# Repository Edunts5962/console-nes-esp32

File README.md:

# Console NES ESP32

Une console NES portable construite autour d'un **ESP32-S3** à écran tactile : émulation des jeux NES avec le son, menus modernes, jeux sur carte microSD ou en mémoire interne, sauvegardes, manette NES filaire **ou téléphone Android comme manette Bluetooth**, **sortie télévision** en vidéo composite grâce à un second ESP32, et portail web pour envoyer les jeux et mettre le logiciel à jour par Wi-Fi.

> Projet amateur, en version bêta. Dérivé du dépôt [Esp32-S3-nes-emulator-by-DSN](https://github.com/derdacavga/Esp32-S3-nes-emulator-by-DSN) (derdacavga), lui-même basé sur le cœur d'émulation **nofrendo**. Aucun jeu n'est fourni.

## Sommaire

- [Fonctionnalités](#fonctionnalités)
- [Matériel](#matériel)
- [Contenu du dépôt](#contenu-du-dépôt)
- [Installation](#installation)
- [Premiers pas](#premiers-pas)
- [Manette sur le téléphone](#manette-sur-le-téléphone)
- [Options de compilation](#options-de-compilation)
- [Limites connues](#limites-connues)
- [Crédits et licences](#crédits-et-licences)

## Fonctionnalités

**Jeux**
- Émulation NES (cœur nofrendo) avec le son ; 49 mappers : 0 à 5, 7 à 11, 15, 16, 18, 19, 21 à 25, 32 à 34, 40 à 42, 46, 50, 64 à 66, 69 à 71, 73, 75, 78, 79, 85, 87, 93, 94, 99, 113, 118, 160, 229, 231, 232. Un jeu non pris en charge est refusé avec un message.
- Jeux sur **carte microSD** et en **mémoire interne** (partition FAT de la flash, ~9,6 Mo) ; jusqu'à **1000 jeux**, affichés par pages de 50.
- **Sauvegardes** : RAM de pile des cartouches (Zelda, Final Fantasy…), sauvegarde instantanée sur 3 emplacements, **reprise automatique** en quittant un jeu.
- **Menu pause** en partie : reprendre, sauvegarder, charger, volume, favoris, jeux récents, changer de jeu sans redémarrer.
- Un jeu qui fait planter la console au lancement est **mis de côté** (dossier `/quarantaine`), récupérable ensuite.

**Interface**
- Menus **LVGL 8** sur l'écran tactile 320 × 240 : liste des jeux avec recherche (clavier à l'écran), favoris, récents, « Reprendre » ; Réglages (luminosité, volume, thèmes de couleurs, Wi-Fi, étalonnage du tactile, aide) ; onglets Vidéo et Portail (QR codes).
- Trois manettes, utilisables ensemble : **zones tactiles** de part et d'autre de l'image, **manette NES filaire** (registre CD4021, prise DB9), **téléphone Android** en Bluetooth LE (page web [`manette8.html`](docs/manette/manette8.html)).
- **Plein écran** automatique quand le téléphone sert de manette.

**Télévision**
- **Sortie vidéo composite couleur** PAL 50 Hz, NTSC ou PAL 60 Hz, image progressive au choix, et son, par un second ESP32 relié en SPI (3 fils).
- Liste des jeux et menu pause affichés sur la télévision.

**Wi-Fi**
- Connexion à la box ou **point d'accès** « NES-WiFi » de la console.
- **Portail web** : envoi de jeux (glisser-déposer), déplacement carte SD ↔ mémoire interne, suppression, recherche de doublons, formatage de la carte SD, jeux écartés, réseau Wi-Fi de la box.
- **Mise à jour du logiciel par Wi-Fi** (fichier `.bin` envoyé au portail) : jeux, sauvegardes et réglages sont conservés.

| Page du téléphone | Portail web |
|---|---|
|  |  |

## Matériel

### Carte principale — LCDWIKI ES3C28P

| | |
|---|---|
| Processeur | **ESP32-S3R8** : 2 cœurs Xtensa LX7 à 240 MHz, 512 Ko de SRAM, **8 Mo de PSRAM** octale (OPI) |
| Flash | **16 Mo** |
| Écran | **ILI9341 2,8"**, 320 × 240, SPI |
| Tactile | **FT6336**, capacitif (I2C) |
| Son | codec **ES8311** (I2C + I2S) et amplificateur, haut-parleur |
| Stockage | lecteur **microSD** (SD_MMC) |
| Radio | Wi-Fi 2,4 GHz, Bluetooth LE |

### Carte vidéo — ESP32 « classique » (facultative)

| | |
|---|---|
| Carte | **Freenove ESP32-WROOM** (module ESP32-WROOM-32E) ou ESP32-DevKitC V4 |
| Processeur | ESP32-D0WD-V3 : 2 cœurs Xtensa LX6 à 240 MHz, 520 Ko de SRAM, 4 Mo de flash |
| Vidéo | composite couleur sur **GPIO25** (DAC intégré), vers l'entrée AV d'un téléviseur ou un convertisseur AV → HDMI |
| Son | **GPIO26** en PWM + filtre RC |

Seul l'ESP32 d'origine a le DAC nécessaire à la vidéo : un ESP32-S2, S3 ou C3 ne convient pas pour cette carte.

### Câblage minimal

| ESP32-S3 (ES3C28P) | | Carte vidéo ESP32 |
|---|---|---|
| GPIO2 (connecteur « Expanded IO ») | SCLK, 330 Ω | IO14 |
| GPIO3 (connecteur « Expanded IO ») | CS, 330 Ω | IO15 |
| GPIO43 / TX0 (connecteur « UART ») | MOSI, 330 Ω | IO13 |
| GND | masse | GND |

Manette NES filaire (3,3 V) : LATCH → GPIO21, CLOCK → GPIO14, DATA → GPIO44 (RX0).

Le document [docs/MATERIEL.md](docs/MATERIEL.md) détaille tout : brochage complet, sortie vidéo (pourquoi GPIO25 va directement à la prise RCA), manette, **carte porteuse KiCad** qui réunit les deux cartes (alimentation 9–12 V, prises RCA, DB9), listes d'achat, mise en service et dépannage.

## Contenu du dépôt

```
console-nes-esp32/
├── firmware/
│   ├── nes_emulator/         croquis de la console (ESP32-S3)
│   └── video_coprocessor/    croquis de la carte vidéo TV (ESP32)
├── prototypes/
│   └── autonome_prototype_v0.4/   essai d'émulateur minimaliste sur un seul ESP32
├── config/
│   ├── lv_conf.h             configuration LVGL 8.3 utilisée
│   └── User_Setup.h          configuration TFT_eSPI de l'écran ES3C28P
├── hardware/kicad/           carte porteuse et manette (KiCad, PDF, nomenclatures, import EasyEDA)
├── docs/
│   ├── MATERIEL.md           matériel, câblage, sortie vidéo, carte porteuse
│   ├── protocole_bluetooth.md  manette du téléphone : utilisation et protocole
│   ├── aide_memoire.html     aide-mémoire des commandes (à imprimer)
│   ├── manette/              page web de la manette du téléphone
│   └── images/
├── CHANGELOG.md
└── LICENSE
```

## Installation

### 1. Outils

- **IDE Arduino 2.x** et le paquet de cartes **esp32 d'Espressif Systems, version 3.x** (compilé avec la 3.3.11).
- Bibliothèques (Gestionnaire de bibliothèques ou copie manuelle dans `Arduino/libraries/`) :

| Bibliothèque | Version | Pour | Configuration |
|---|---|---|---|
| **lvgl** | **8.3.11** (pas la 9.x) | console | copier [`config/lv_conf.h`](config/lv_conf.h) dans `Arduino/libraries/`, à côté du dossier `lvgl` |
| **TFT_eSPI** | 2.5.43 | console | remplacer `Arduino/libraries/TFT_eSPI/User_Setup.h` par [`config/User_Setup.h`](config/User_Setup.h) |
| **LovyanGFX** | 1.2.x | carte vidéo | aucune |

Wi-Fi, Bluetooth, serveur web, mise à jour OTA, NVS, SD_MMC et FFat sont fournis par le paquet esp32.

### 2. Identifiants Wi-Fi

Dans `firmware/nes_emulator/`, copier `wifi_config.example.h` en **`wifi_config.h`** et y mettre le nom et le mot de passe de la box ; changer aussi le mot de passe du point d'accès `NES-WiFi` (8 caractères au moins). `wifi_config.h` est ignoré par git : il ne part pas sur le dépôt. Sans lui, le croquis compile avec le modèle (le point d'accès reste utilisable, et le réseau de la box peut être saisi plus tard dans le portail).

### 3. Console (ESP32-S3)

Ouvrir `firmware/nes_emulator/nes_emulator.ino`, puis dans le menu **Outils** :

| Réglage | Valeur |
|---|---|
| Carte | **ESP32S3 Dev Module** |
| USB CDC On Boot | **Enabled** (le port série passe par l'USB ; GPIO43/44 restent libres pour la liaison vidéo et la manette) |
| Flash Size | **16MB (128Mb)** |
| Partition Scheme | **16M Flash (3MB APP/9.9MB FATFS)** |
| PSRAM | **OPI PSRAM** |

Téléverser. Si le téléversement échoue : maintenir BOOT, appuyer sur RESET, relâcher BOOT.

Avec arduino-cli :

```sh
arduino-cli compile -b "esp32:esp32:esp32s3:PSRAM=opi,FlashSize=16M,CDCOnBoot=cdc,PartitionScheme=app3M_fat9M_16MB" firmware/nes_emulator
```

**Sans carte vidéo**, mettre `ENABLE_VIDEO_LINK` à 0 dans `video_link.h`.

### 4. Carte vidéo (ESP32)

Ouvrir `firmware/video_coprocessor/video_coprocessor.ino`, carte **ESP32 Dev Module**, bibliothèque LovyanGFX, téléverser. Sans console branchée, la télévision affiche « En attente de la console » avec une mire de couleurs ; un appui long sur BOOT change la norme (PAL 50 → NTSC → PAL 60).

```sh
arduino-cli compile -b esp32:esp32:esp32 firmware/video_coprocessor
```

## Premiers pas

1. **Jeux** : copier des fichiers `.nes` à la **racine** d'une carte microSD formatée en **FAT32**, ou les envoyer plus tard par le portail (carte SD ou mémoire interne).
2. **Premier démarrage** : l'écran demande d'étalonner le tactile (toucher 3 croix, puis une croix de vérification).
3. **Jouer** : toucher un jeu. Un appui long ouvre sa fiche (favori, reprendre, supprimer).

| Commande | Pendant le jeu |
|---|---|
| SELECT + START tenus 1 s | menu pause (écran ou télévision) |
| doigt posé 1 s sur l'image | menu pause (écran tactile) |
| SELECT + haut / bas | volume ±5 % |
| SELECT tenu 3 s | retour au menu de la console (la partie est gardée) |

Toutes les commandes sont dans Réglages (aide « Commandes ») et dans l'[aide-mémoire](docs/aide_memoire.html) à imprimer.

### Portail web

1. Réglages > Wi-Fi : allumer le Wi-Fi (mode Auto : la box, puis le point d'accès si elle ne répond pas).
2. L'onglet **Portail** affiche l'adresse et un QR code. En point d'accès : rejoindre le réseau **`NES-WiFi`** (mot de passe défini dans `wifi_config.h`), puis ouvrir **http://192.168.4.1/**.

Le Wi-Fi est coupé au lancement d'un jeu, et il ne fonctionne pas en même temps que la manette Bluetooth (mémoire de l'ESP32-S3 insuffisante pour les deux).

### Mise à jour du logiciel par Wi-Fi

Dans l'IDE Arduino : **Croquis > Exporter les binaires compilés**, puis envoyer le fichier `nes_emulator.ino.bin` dans la section « Mettre à jour le logiciel » du portail. La console redémarre sur la nouvelle version ; jeux, sauvegardes et réglages sont conservés.

> Les fichiers `.bin` compilés contiennent les identifiants Wi-Fi de `wifi_config.h` : ne pas les publier (ils sont ignorés par git).

## Manette sur le téléphone

La page [`docs/manette/manette8.html`](docs/manette/manette8.html) utilise **Web Bluetooth**, qui exige **Chrome sur Android** et une page servie en **HTTPS**. GitHub Pages s'en charge :

1. Sur GitHub, dépôt > **Settings > Pages** ; *Source* : **Deploy from a branch**, branche **main**, dossier **/docs**, *Save*.
2. Quelques minutes plus tard, la page est disponible à l'adresse
   `https://<pseudo>.github.io/console-nes-esp32/manette/manette8.html`.
3. L'ouvrir dans Chrome sur le téléphone (Bluetooth et localisation activés), **CONNECTER**, choisir **`NES-ESP32S3`**. Chrome > ⋮ > « Ajouter à l'écran d'accueil » l'installe comme une application.

Utilisation et protocole : [docs/protocole_bluetooth.md](docs/protocole_bluetooth.md).

## Options de compilation

| Fichier | Option | Défaut | Rôle |
|---|---|---|---|
| `hw_config.h` | `HAS_PHYSICAL_CONTROLLER` | 0 | 1 = manette filaire branchée |
| `hw_config.h` | `PAD_PROTOCOL` | `PAD_PROTOCOL_NES` | manette NES (CD4021) ou montage 74HC165 |
| `hw_config.h` | `USE_TOUCH_CONTROLS` | 1 | zones tactiles pendant le jeu |
| `hw_config.h` | `ENABLE_BLE_GAMEPAD` | 1 | manette du téléphone (0 : pile Bluetooth non compilée, ~230 Ko de moins) |
| `hw_config.h` | `LCD_FULLSCREEN_MODE` | 1 | plein écran : 0 jamais, 1 avec le téléphone, 2 toujours |
| `hw_config.h` | `LCD_FULLSCREEN_CROP_LINES` | 8 | lignes retirées en haut et en bas en plein écran |
| `hw_config.h` | `LCD_GAME_COLOR_FIX` | 1 | ordre des octets des couleurs du jeu sur l'écran |
| `hw_config.h` | `USE_LVGL_UI` | 1 | 0 = ancienne interface dessinée à la main |
| `video_link.h` | `ENABLE_VIDEO_LINK` | 1 | liaison vers la carte vidéo (0 sans carte vidéo) |
| `wifi_boot.h` | `ENABLE_WIFI_PORTAL` | 1 | Wi-Fi et portail web |
| `wifi_boot.h` | `WIFI_START_AT_BOOT` | 0 | 1 = connexion Wi-Fi pendant le logo |
| `video_coprocessor.ino` | `VIDEO_OUTPUT_LEVEL` | 128 | amplitude vidéo : 160–200 si l'image est sombre, 100–110 si elle est trop claire |

## Limites connues

- Logiciel en **version bêta**. Selon les jeux, l'émulateur saute des images pour garder la vitesse du jeu.
- Wi-Fi et Bluetooth ne fonctionnent pas en même temps (le Bluetooth est arrêté tant que le Wi-Fi est allumé).
- Web Bluetooth : Chrome sur Android uniquement (Safari sur iPhone ne le propose pas).
- La **carte porteuse KiCad** est placée mais **pas routée**, et n'a pas été fabriquée.
- Le prototype « autonome » (un seul ESP32) valide le matériel mais n'exécute pas encore de jeu.

## Crédits et licences

- Ce projet est distribué sous licence **GNU GPL v3** ([LICENSE](LICENSE)), comme le dépôt d'origine [derdacavga/Esp32-S3-nes-emulator-by-DSN](https://github.com/derdacavga/Esp32-S3-nes-emulator-by-DSN).
- Cœur d'émulation **nofrendo** © 1998-2000 Matthew Conte, repris via [esp32-nesemu](https://github.com/espressif/esp32-nesemu) d'Espressif : licence GNU LGPL v2 ([LICENSES/LGPL-2.0.txt](LICENSES/LGPL-2.0.txt)), mention de licence d'origine au début de chaque fichier repris.
- Pilote du codec **ES8311** : Espressif Systems, licence Apache-2.0 (en-têtes SPDX conservés, [LICENSES/Apache-2.0.txt](LICENSES/Apache-2.0.txt)).
- Générateur de **QR code** : Project Nayuki, licence MIT (texte dans `nes_qrcodegen.c/.h`).
- Sortie vidéo composite : adaptation de `Panel_CVBS` de [LovyanGFX](https://github.com/lovyan03/LovyanGFX) (lovyan03 et contributeurs), licence FreeBSD (`firmware/video_coprocessor/LICENCE_LovyanGFX.txt`) ; inspirée de [ESP_8_BIT_composite](https://github.com/Roger-random/ESP_8_BIT_composite) (Roger Cheng) et [esp_8_bit](https://github.com/rossumur/esp_8_bit) (rossum).
- Polices de l'interface : **Montserrat** (SIL Open Font License 1.1) et symboles **Font Awesome Free** (SIL OFL 1.1 / CC BY 4.0), converties par lv_font_conv. Polices de la carte vidéo : Adobe Helvetica (polices X11), extraites de [U8g2](https://github.com/olikraus/u8g2).
- Bibliothèques : [LVGL](https://lvgl.io) (MIT, `config/lv_conf.h` dérivé de son modèle), [TFT_eSPI](https://github.com/Bodmer/TFT_eSPI) (Bodmer).
- Détail fichier par fichier : [NOTICE](NOTICE) ; textes des licences : dossier [LICENSES](LICENSES).

## Avertissement

NES et Nintendo sont des marques de Nintendo. Ce projet n'est ni affilié à Nintendo ni approuvé par Nintendo. **Aucun jeu n'est fourni** : n'utilisez que des jeux dont vous avez le droit de vous servir (jeux libres « homebrew », copies de vos propres cartouches selon la loi de votre pays).

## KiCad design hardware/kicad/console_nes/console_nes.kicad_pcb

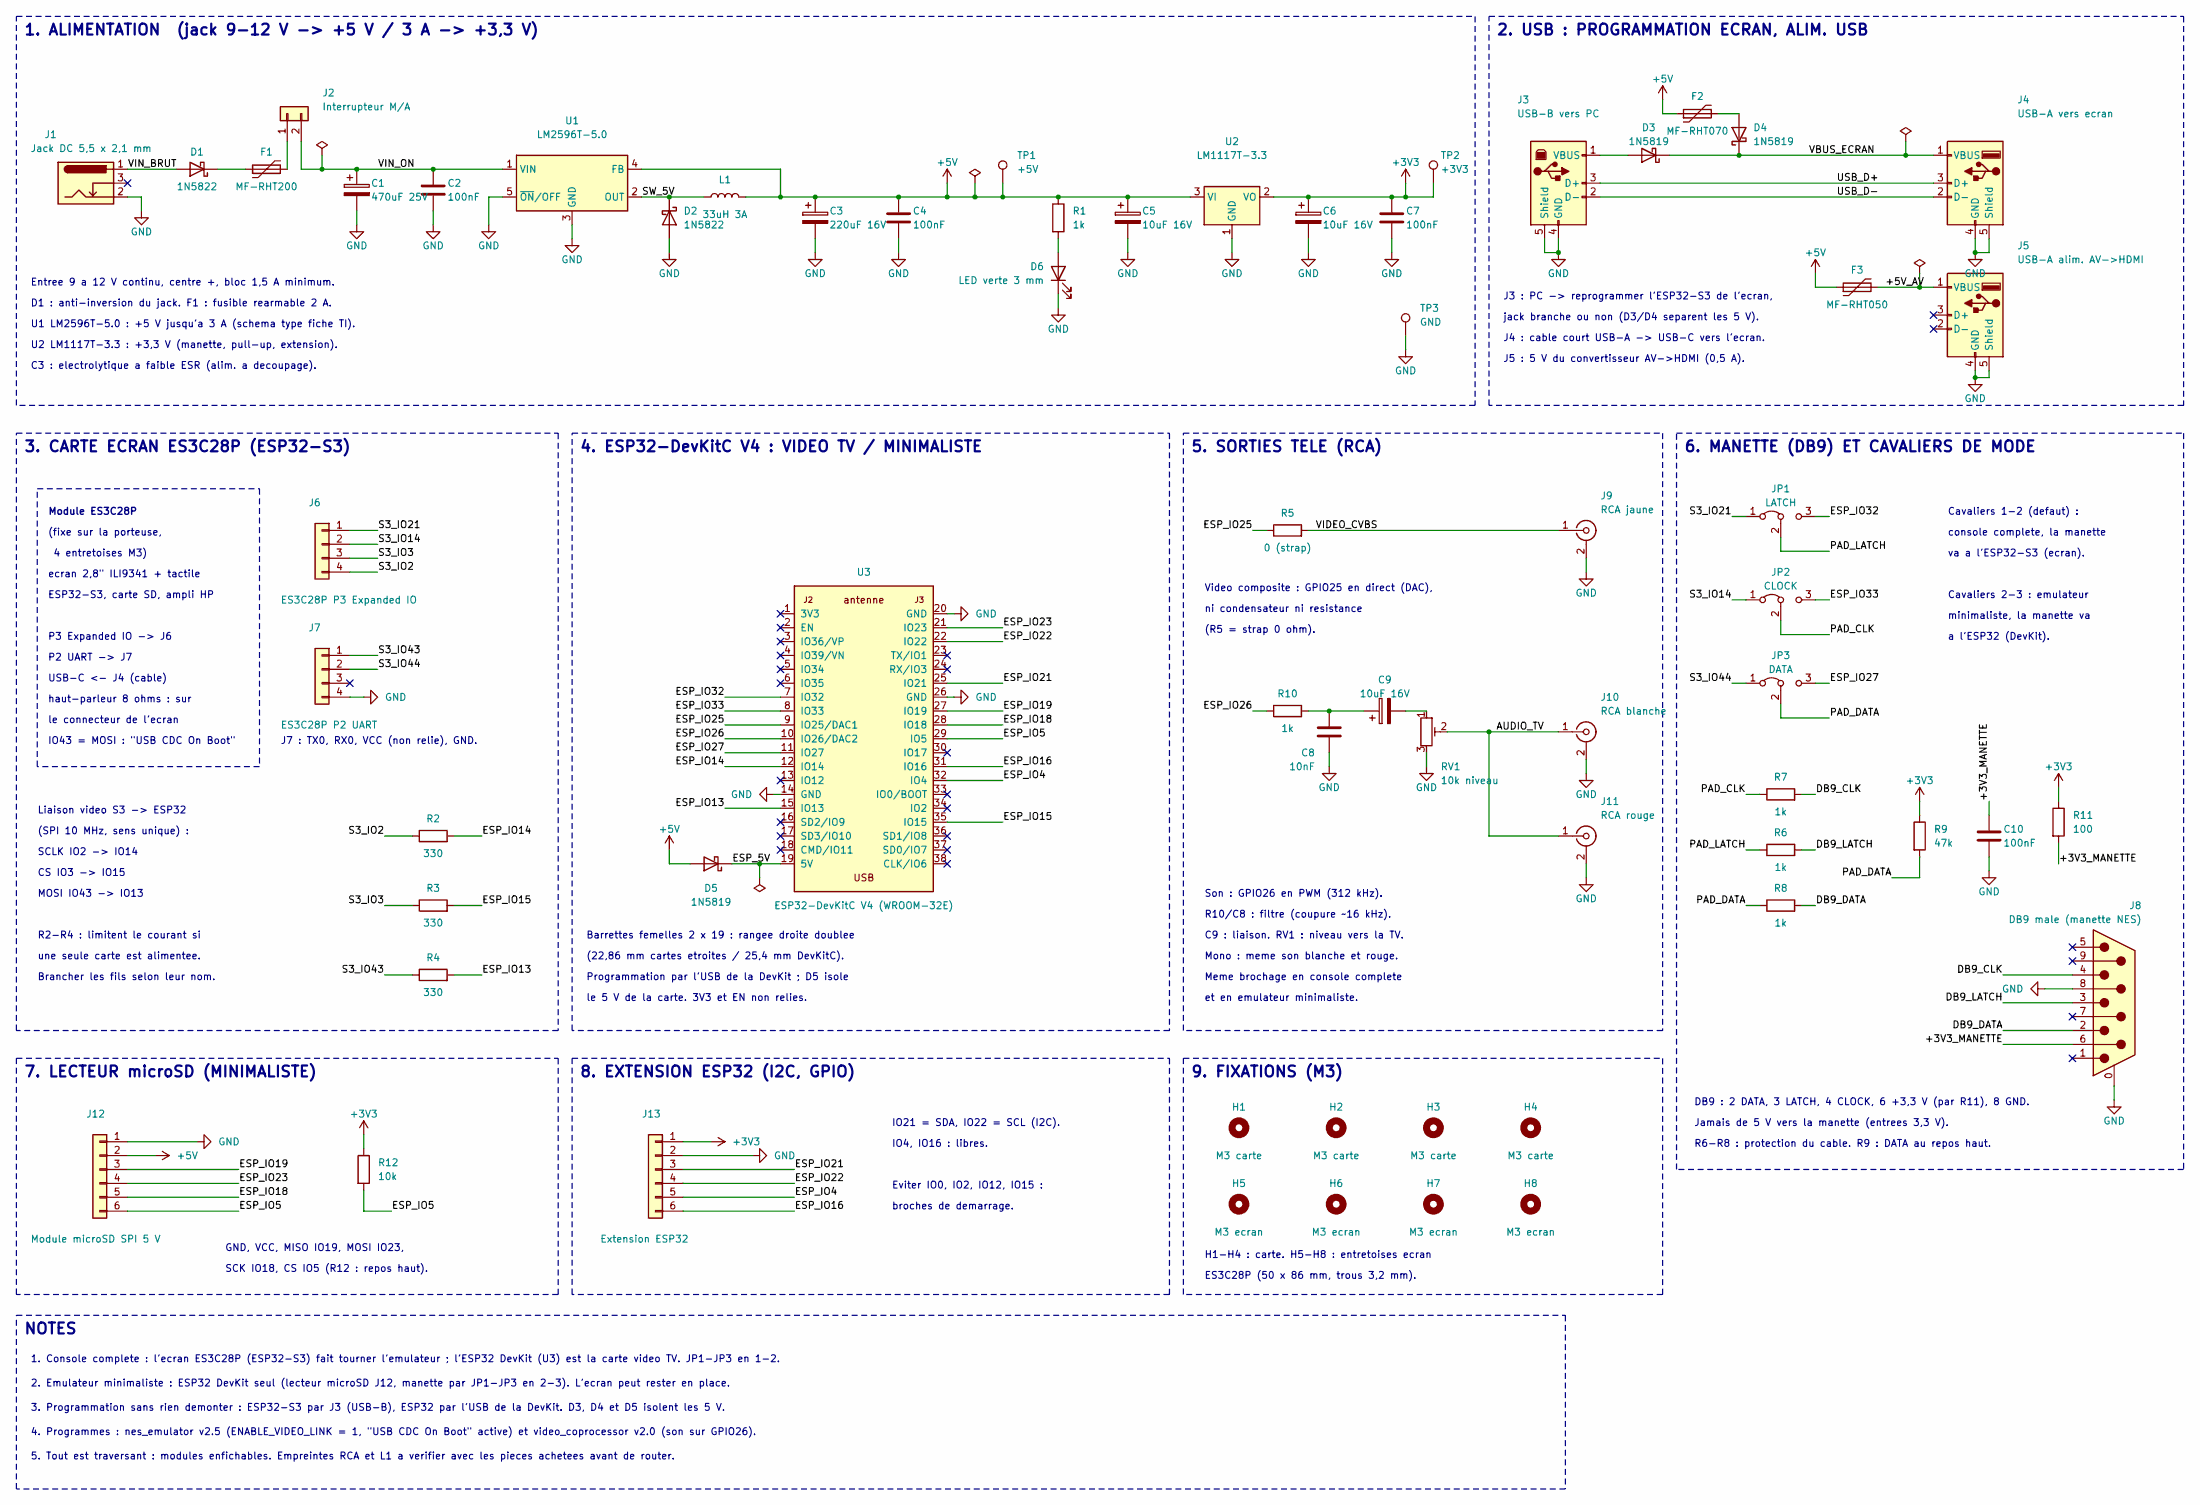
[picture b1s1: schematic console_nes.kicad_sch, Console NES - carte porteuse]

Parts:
C1: 470uF 25V; CP_Radial_D10.0mm_P5.00mm
C2, C4, C7, C10: 100nF; C_Disc_D5.0mm_W2.5mm_P5.00mm
C3: 220uF 16V; CP_Radial_D8.0mm_P3.50mm
C5, C6, C9: 10uF 16V; CP_Radial_D5.0mm_P2.00mm
C8: 10nF; C_Disc_D5.0mm_W2.5mm_P5.00mm
D1, D2: 1N5822; D_DO-201AD_P15.24mm_Horizontal
D3, D4, D5: 1N5819; D_DO-41_SOD81_P10.16mm_Horizontal
D6: LED verte 3 mm; LED_D3.0mm
F1: MF-RHT200; Fuse_Bourns_MF-RHT200
F2: MF-RHT070; Fuse_Bourns_MF-RHT070
F3: MF-RHT050; Fuse_Bourns_MF-RHT050
H1, H2, H3, H4: M3 carte; MountingHole_3.2mm_M3
H5, H6, H7, H8: M3 ecran; MountingHole_3.2mm_M3
J1: Jack DC 5,5 x 2,1 mm; BarrelJack_Horizontal
J2: Interrupteur M/A; JST_XH_B2B-XH-A_1x02_P2.50mm_Vertical
J3: USB-B vers PC; USB_B_OST_USB-B1HSxx_Horizontal
J4: USB-A vers ecran; USB_A_Molex_67643_Horizontal
J5: USB-A alim. AV->HDMI; USB_A_Molex_67643_Horizontal
J6: ES3C28P P3 Expanded IO; PinHeader_1x04_P2.54mm_Vertical
J7: ES3C28P P2 UART; PinHeader_1x04_P2.54mm_Vertical
J8: DB9 male (manette NES); DSUB-9_Male_Horizontal_P2.77x2.84mm_EdgePinOffset7.70mm_Hou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
J9: RCA jaune; RCA_Jack_CUI_RCJ-01x_Horizontal
J10: RCA blanche; RCA_Jack_CUI_RCJ-01x_Horizontal
J11: RCA rouge; RCA_Jack_CUI_RCJ-01x_Horizontal
J12: Module microSD SPI 5 V; PinSocket_1x06_P2.54mm_Vertical
J13: Extension ESP32; PinHeader_1x06_P2.54mm_Vertical
JP1: LATCH; PinHeader_1x03_P2.54mm_Vertical
JP2: CLOCK; PinHeader_1x03_P2.54mm_Vertical
JP3: DATA; PinHeader_1x03_P2.54mm_Vertical
L1: 33uH 3A; L_Radial_D12.0mm_P6.00mm_Murata_1900R
R1, R6, R7, R8, R10: 1k; R_Axial_DIN0207_L6.3mm_D2.5mm_P10.16mm_Horizontal
R2, R3, R4: 330; R_Axial_DIN0207_L6.3mm_D2.5mm_P10.16mm_Horizontal
R5: 0 (strap); R_Axial_DIN0207_L6.3mm_D2.5mm_P10.16mm_Horizontal
R9: 47k; R_Axial_DIN0207_L6.3mm_D2.5mm_P10.16mm_Horizontal
R11: 100; R_Axial_DIN0207_L6.3mm_D2.5mm_P10.16mm_Horizontal
R12: 10k; R_Axial_DIN0207_L6.3mm_D2.5mm_P10.16mm_Horizontal
RV1: 10k niveau; Potentiometer_Bourns_3386P_Vertical
TP1: +5V; TestPoint_Loop_D2.50mm_Drill1.0mm
TP2: +3V3; TestPoint_Loop_D2.50mm_Drill1.0mm
TP3: GND; TestPoint_Loop_D2.50mm_Drill1.0mm
U1: LM2596T-5.0; TO-220-5_P3.4x3.7mm_StaggerOdd_Lead3.8mm_Vertical
U2: LM1117T-3.3; TO-220-3_Vertical
U3: ESP32-DevKitC V4 (WROOM-32E); ESP32_DevKitC_V4_Socket_3rows

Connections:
+3V3: C6.1, C7.1, J13.1, R9.1, R11.1, R12.1, TP2.1, U2.2 (VO)
+5V: C3.1, C4.1, C5.1, D5.2 (A), F2.1, F3.1, J12.2, L1.2, R1.1, TP1.1, U1.4 (FB), U2.3 (VI)
/+3V3_MANETTE: C10.1, J8.6, R11.2
/+5V_AV: F3.2, J5.1 (VBUS)
/AUDIO_TV: J10.1 (In), J11.1 (In), RV1.2
/DB9_CLK: J8.4, R7.2
/DB9_DATA: J8.2, R8.2
/DB9_LATCH: J8.3, R6.2
/ESP_5V: D5.1 (K), U3.19 (5V)
/ESP_IO4: J13.5, U3.32 (IO4)
/ESP_IO5: J12.6, R12.2, U3.29 (IO5)
/ESP_IO13: R4.2, U3.15 (IO13)
/ESP_IO14: R2.2, U3.12 (IO14)
/ESP_IO15: R3.2, U3.35 (IO15)
/ESP_IO16: J13.6, U3.31 (IO16)
/ESP_IO18: J12.5, U3.28 (IO18)
/ESP_IO19: J12.3, U3.27 (IO19)
/ESP_IO21: J13.3, U3.25 (IO21)
/ESP_IO22: J13.4, U3.22 (IO22)
/ESP_IO23: J12.4, U3.21 (IO23)
/ESP_IO25: R5.1, U3.9 (IO25/DAC1)
/ESP_IO26: R10.1, U3.10 (IO26/DAC2)
/ESP_IO27: JP3.3 (B), U3.11 (IO27)
/ESP_IO32: JP1.3 (B), U3.7 (IO32)
/ESP_IO33: JP2.3 (B), U3.8 (IO33)
/PAD_CLK: JP2.2 (C), R7.1
/PAD_DATA: JP3.2 (C), R8.1, R9.2
/PAD_LATCH: JP1.2 (C), R6.1
/S3_IO2: J6.4, R2.1
/S3_IO3: J6.3, R3.1
/S3_IO14: J6.2, JP2.1 (A)
/S3_IO21: J6.1, JP1.1 (A)
/S3_IO43: J7.1, R4.1
/S3_IO44: J7.2, JP3.1 (A)
/SW_5V: D2.1 (K), L1.1, U1.2 (OUT)
/USB_D+: J3.3 (D+), J4.3 (D+)
/USB_D-: J3.2 (D-), J4.2 (D-)
/VBUS_ECRAN: D3.1 (K), D4.1 (K), J4.1 (VBUS)
/VIDEO_CVBS: J9.1 (In), R5.2
/VIN_BRUT: D1.2 (A), J1.1
/VIN_ON: C1.1, C2.1, J2.2, U1.1 (VIN)
GND: C1.2, C2.2, C3.2, C4.2, C5.2, C6.2, C7.2, C8.2, C10.2, D2.2 (A), D6.1 (K), J1.2, J3.4 (GND), J3.5 (Shield), J4.4 (GND), J4.5 (Shield), J5.4 (GND), J5.5 (Shield), J7.4, J8.0 (PAD), J8.8, J9.2 (Ext), J10.2 (Ext), J11.2 (Ext), J12.1, J13.2, RV1.3, TP3.1, U1.3 (GND), U1.5 (~ON/OFF), U2.1 (GND), U3.14 (GND), U3.20 (GND), U3.26 (GND)
unnamed: C8.1, C9.1, R10.2
unnamed: C9.2, RV1.1
unnamed: D1.1 (K), F1.1
unnamed: D3.2 (A), J3.1 (VBUS)
unnamed: D4.2 (A), F2.2
unnamed: D6.2 (A), R1.2
unnamed: F1.2, J2.1

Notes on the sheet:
1. ALIMENTATION (jack 9-12 V -> +5 V / 3 A -> +3,3 V)
Entree 9 a 12 V continu, centre +, bloc 1,5 A minimum.
D1 : anti-inversion du jack. F1 : fusible rearmable 2 A.
U1 LM2596T-5.0 : +5 V jusqu'a 3 A (schema type fiche TI).
U2 LM1117T-3.3 : +3,3 V (manette, pull-up, extension).
C3 : electrolytique a faible ESR (alim. a decoupage).
2. USB : PROGRAMMATION ECRAN, ALIM. USB
J3 : PC -> reprogrammer l'ESP32-S3 de l'ecran,
jack branche ou non (D3/D4 separent les 5 V).
J4 : cable court USB-A -> USB-C vers l'ecran.
J5 : 5 V du convertisseur AV->HDMI (0,5 A).
3. CARTE ECRAN ES3C28P (ESP32-S3)
Module ES3C28P
(fixe sur la porteuse,
4 entretoises M3)
ecran 2,8" ILI9341 + tactile
ESP32-S3, carte SD, ampli HP
P3 Expanded IO -> J6
P2 UART -> J7
USB-C <- J4 (cable)
haut-parleur 8 ohms : sur
le connecteur de l'ecran
IO43 = MOSI : "USB CDC On Boot"
J7 : TX0, RX0, VCC (non relie), GND.
Liaison video S3 -> ESP32
(SPI 10 MHz, sens unique) :
SCLK IO2 -> IO14
CS IO3 -> IO15
MOSI IO43 -> IO13
R2-R4 : limitent le courant si
une seule carte est alimentee.
Brancher les fils selon leur nom.
4. ESP32-DevKitC V4 : VIDEO TV / MINIMALISTE
Barrettes femelles 2 x 19 : rangee droite doublee
(22,86 mm cartes etroites / 25,4 mm DevKitC).
Programmation par l'USB de la DevKit ; D5 isole
le 5 V de la carte. 3V3 et EN non relies.
5. SORTIES TELE (RCA)
Video composite : GPIO25 en direct (DAC),
ni condensateur ni resistance

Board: 2 copper layers, 63 parts (0 on the bottom side), 49 nets, no tracks yet.

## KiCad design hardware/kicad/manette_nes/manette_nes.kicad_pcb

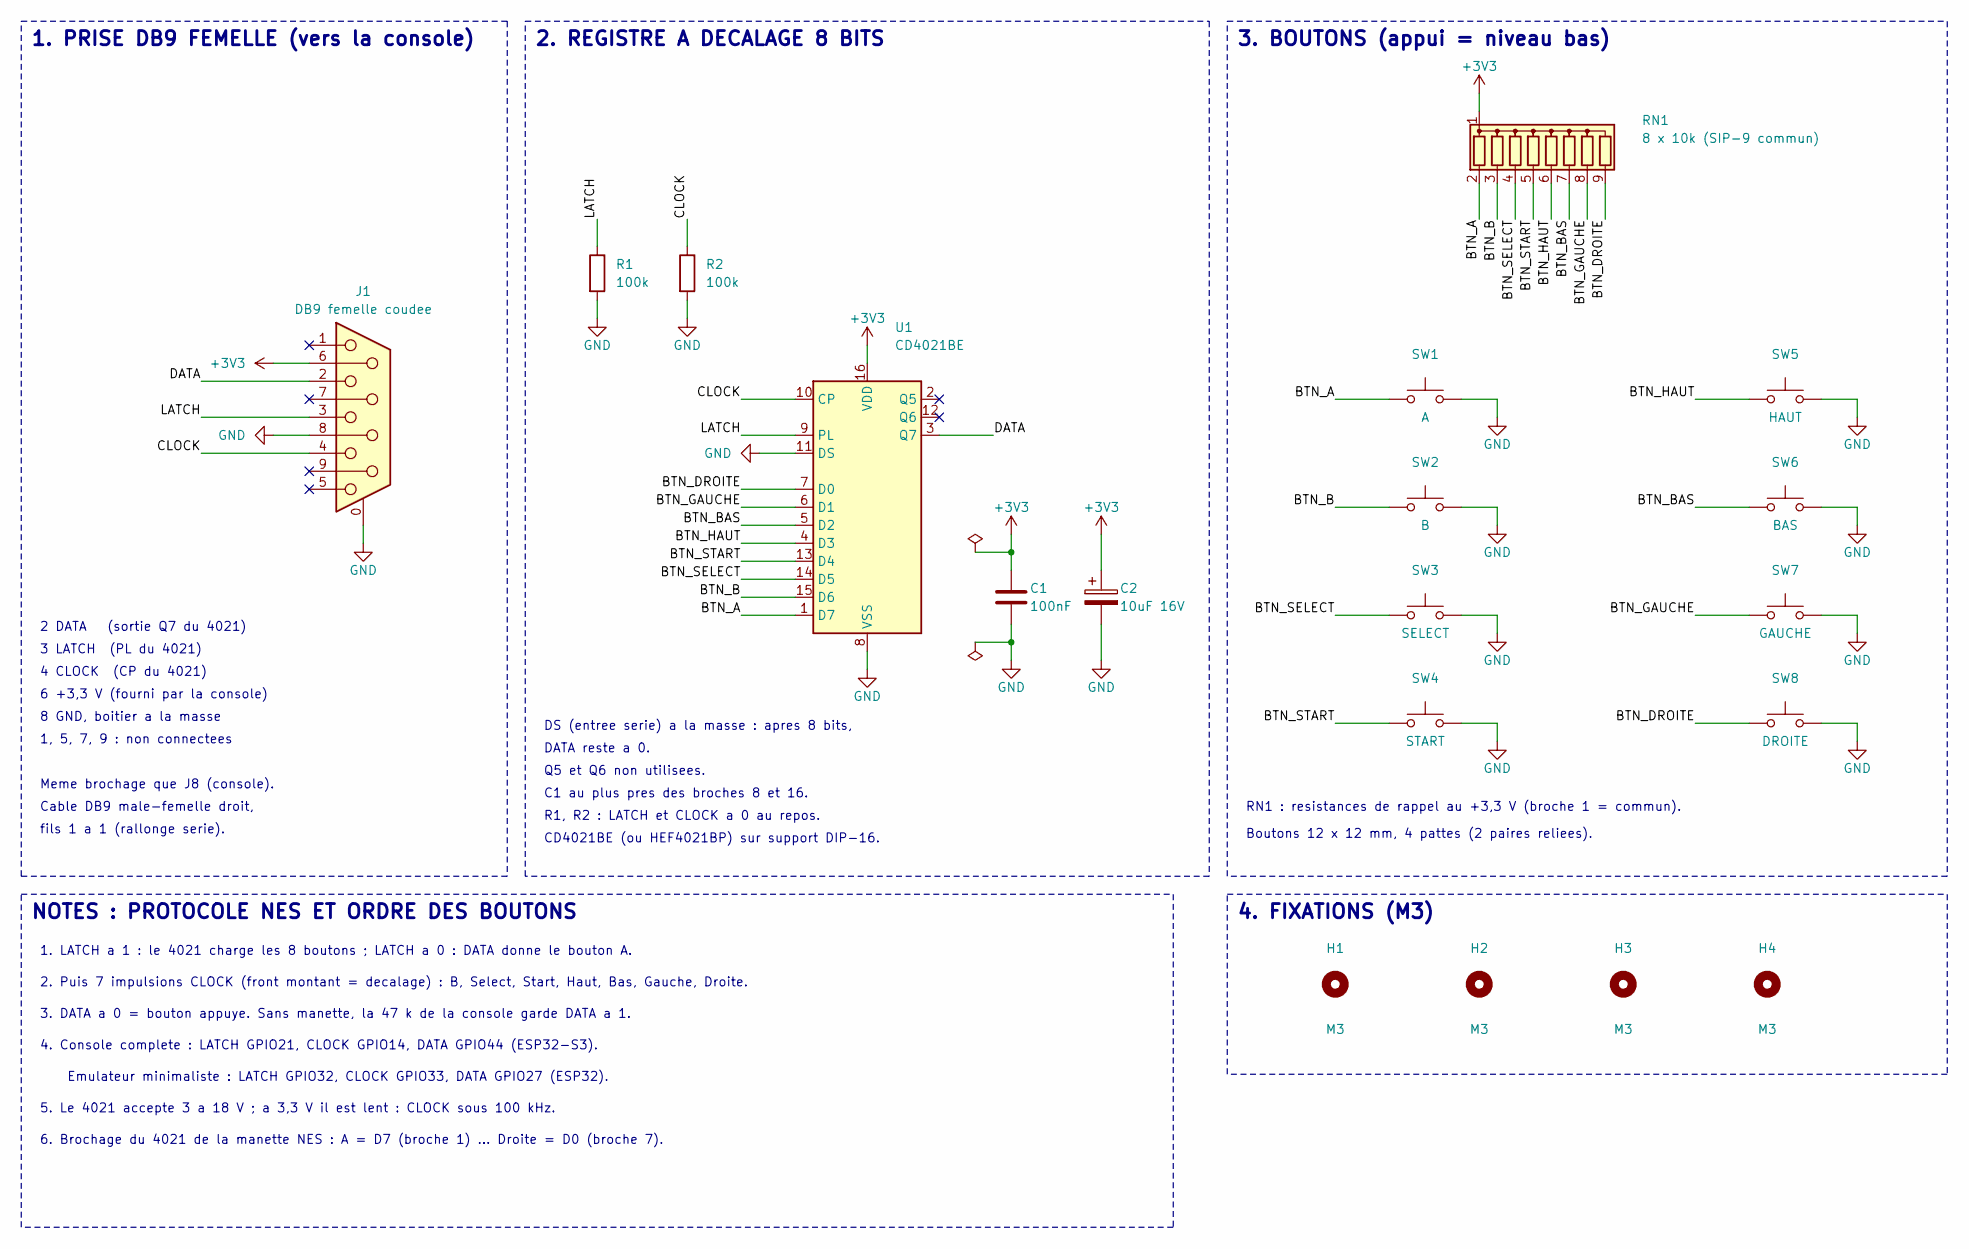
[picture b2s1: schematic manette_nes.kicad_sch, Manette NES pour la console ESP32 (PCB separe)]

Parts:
C1: 100nF; C_Disc_D5.0mm_W2.5mm_P5.00mm
C2: 10uF 16V; CP_Radial_D5.0mm_P2.00mm
H1, H2, H3, H4: M3; MountingHole_3.2mm_M3
J1: DB9 femelle coudee; DSUB-9_Female_Horizontal_P2.77x2.84mm_EdgePinOffset7.70mm_H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
R1, R2: 100k; R_Axial_DIN0207_L6.3mm_D2.5mm_P10.16mm_Horizontal
RN1: 8 x 10k (SIP-9 commun); R_Array_SIP9
SW1: A; SW_PUSH-12mm_Wuerth-430476085716
SW2: B; SW_PUSH-12mm_Wuerth-430476085716
SW3: SELECT; SW_PUSH-12mm_Wuerth-430476085716
SW4: START; SW_PUSH-12mm_Wuerth-430476085716
SW5: HAUT; SW_PUSH-12mm_Wuerth-430476085716
SW6: BAS; SW_PUSH-12mm_Wuerth-430476085716
SW7: GAUCHE; SW_PUSH-12mm_Wuerth-430476085716
SW8: DROITE; SW_PUSH-12mm_Wuerth-430476085716
U1: CD4021BE; DIP-16_W7.62mm_Socket

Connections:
+3V3: C1.1, C2.1, J1.6, RN1.1 (common), U1.16 (VDD)
/BTN_A: RN1.2 (R1), SW1.1, U1.1 (D7)
/BTN_B: RN1.3 (R2), SW2.1, U1.15 (D6)
/BTN_BAS: RN1.7 (R6), SW6.1, U1.5 (D2)
/BTN_DROITE: RN1.9 (R8), SW8.1, U1.7 (D0)
/BTN_GAUCHE: RN1.8 (R7), SW7.1, U1.6 (D1)
/BTN_HAUT: RN1.6 (R5), SW5.1, U1.4 (D3)
/BTN_SELECT: RN1.4 (R3), SW3.1, U1.14 (D5)
/BTN_START: RN1.5 (R4), SW4.1, U1.13 (D4)
/CLOCK: J1.4, R2.1, U1.10 (CP)
/DATA: J1.2, U1.3 (Q7)
/LATCH: J1.3, R1.1, U1.9 (PL)
GND: C1.2, C2.2, J1.0 (PAD), J1.8, R1.2, R2.2, SW1.2, SW2.2, SW3.2, SW4.2, SW5.2, SW6.2, SW7.2, SW8.2, U1.8 (VSS), U1.11 (DS)

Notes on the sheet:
1. PRISE DB9 FEMELLE (vers la console)
2 DATA (sortie Q7 du 4021)
3 LATCH (PL du 4021)
4 CLOCK (CP du 4021)
6 +3,3 V (fourni par la console)
8 GND, boitier a la masse
1, 5, 7, 9 : non connectees
Meme brochage que J8 (console).
Cable DB9 male-femelle droit,
fils 1 a 1 (rallonge serie).
2. REGISTRE A DECALAGE 8 BITS
DS (entree serie) a la masse : apres 8 bits,
DATA reste a 0.
Q5 et Q6 non utilisees.
C1 au plus pres des broches 8 et 16.
R1, R2 : LATCH et CLOCK a 0 au repos.
CD4021BE (ou HEF4021BP) sur support DIP-16.
3. BOUTONS (appui = niveau bas)
RN1 : resistances de rappel au +3,3 V (broche 1 = commun).
Boutons 12 x 12 mm, 4 pattes (2 paires reliees).
NOTES : PROTOCOLE NES ET ORDRE DES BOUTONS
1. LATCH a 1 : le 4021 charge les 8 boutons ; LATCH a 0 : DATA donne le bouton A.
2. Puis 7 impulsions CLOCK (front montant = decalage) : B, Select, Start, Haut, Bas, Gauche, Droite.
3. DATA a 0 = bouton appuye. Sans manette, la 47 k de la console garde DATA a 1.
4. Console complete : LATCH GPIO21, CLOCK GPIO14, DATA GPIO44 (ESP32-S3).
Emulateur minimaliste : LATCH GPIO32, CLOCK GPIO33, DATA GPIO27 (ESP32).
5. Le 4021 accepte 3 a 18 V ; a 3,3 V il est lent : CLOCK sous 100 kHz.
6. Brochage du 4021 de la manette NES : A = D7 (broche 1) ... Droite = D0 (broche 7).
4. FIXATIONS (M3)

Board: 2 copper layers, 19 parts (0 on the bottom side), 13 nets, no tracks yet.

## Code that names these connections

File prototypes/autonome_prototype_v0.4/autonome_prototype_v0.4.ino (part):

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//
// ALIGNEMENT SUR LA CARTE PORTEUSE KICAD (console_nes) :
//   - MANETTE : protocole NES (manette KiCad "manette_nes" a CD4021BE, ou
//     manette NES alimentee en 3,3 V) : LATCH GPIO32 (actif haut), CLOCK
//     GPIO33, DATA GPIO27 - cavaliers JP1 a JP3 de la carte porteuse en
//     position 2-3. Ordre : A, B, Select, Start, Haut, Bas, Gauche, Droite.
//   - SON : GPIO26 est reserve au son (filtre R10/C8, C9, RV1 et prises RCA
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// BROCHAGE (carte porteuse KiCad, U3 = ESP32-DevKitC V4) :
//   GPIO25 -> RCA jaune (direct)          GPIO26 -> son (reserve)
//   microSD J12 : SCK=18 MISO=19 MOSI=23 CS=5 (R12 : rappel de CS au 3,3 V)
//   Manette DB9 J8 via JP1-JP3 en 2-3 : LATCH=32 CLOCK=33 DATA=27
//
// Prototype : compile avec le coeur Arduino-ESP32 3.3 et LovyanGFX 1.2, a
// valider pas a pas (moniteur serie pour la SD et la manette, navigateur
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// rappel interne) fait lire "aucun bouton appuye".
#define HAS_PHYSICAL_CONTROLLER 0

#define PAD_LATCH 32   // -> JP1 (2-3) -> R6 -> DB9 broche 3
#define PAD_CLOCK 33   // -> JP2 (2-3) -> R7 -> DB9 broche 4
#define PAD_DATA  27   // <- JP3 (2-3) <- R8 <- DB9 broche 2
#define PAD_LATCH_US 12
#define PAD_HALF_US   6

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
#if HAS_PHYSICAL_CONTROLLER
static void controller_init() {
  pinMode(PAD_LATCH, OUTPUT);
  pinMode(PAD_CLOCK, OUTPUT);
  pinMode(PAD_DATA, INPUT_PULLUP);
  digitalWrite(PAD_LATCH, LOW);
  digitalWrite(PAD_CLOCK, LOW);
}
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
